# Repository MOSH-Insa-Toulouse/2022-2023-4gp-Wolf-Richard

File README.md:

# 2022-2023-4gp-Wolf-Richard

## General Description

One of our projects as part of our 4th year at INSA Toulouse in physical engineering is to create a measuring system for a paper and graphite based strain sensor. We must be able to measure the resistance of this sensor and send it to an android app.

To that we added some elements. One can choose the best gain setting for their sensor thanks to the digital potentiometer controlled by the nunchuk and helped by the OLED screen. The Nunchuk is here to choose the calibrated value for the digital potentiometer. Then, the resistance of the strain gauge is sent to an Android app thanks to a Bluetooth module.

## Deliverables

- PCB shield for Arduino Uno
- Arduino code
- Android APK
- Test bench and protocole used to test the sensor
- Datasheet

## Software versions

- KiCad 6.0.11-0
- Arduino 2.0.4
- MIT app inventor nb192

## PCB shield for Arduino Uno

The whole circuit can be seen in the picture below. Only the pins that are connected to the circuit are welded to the PCB.

## Test Bench and protocole used to test the sensor

The test bench used is shown in the following picture.

To test the sensor, we put it on the bench and try to make it take the shape of the bench as much as possible. We payed attention not to touch the graphite or the aligator clips for the test to be reliable. We took the measurments once we had a stable contact with the bench and a stable value. To determine the displacement of the sensor we used the formula:

displacement = thickness / 2*R_curvature

## User Manual of the circuit and the app

When the arduino is plugged in the program starts automatically.

First, the user needs to calibrate the circuit based on its sensor. Flatten the sensor as much as you can and try to find the best level of the potentiometer to optimise the sensor’s response. To do so, push up on the nunchuk to increase the potentiometer value or push down to decrease. When satisfied, push the C button.

Second, the user is invited to put the sensor in the most deflected position of the test that they want to do and to press C again. This allows for the deflection percentage to be shown on the OLED screen.

From that moment on, the Bluetooth module sends the value of the resistance that was calculated in the program. Thanks to the app one can retrieve the value and see its evolution.

On the app of which you can see a screenshot below, one must first connect to the right Bluetooth module with the button "Let’s go Bluetooth". Once confirmed that the connection was done properly, the toggle "Tic tac boom", which controls the clock, must be on to receive the values. The values are sent by the Bluetooth module every 500ms. The button "Send to Grisolia" saves a text file with the values of the resistance in it. It is only clickable when the clock is off.

One can also select a point on the graph and see its value in the orange box. Above is displayed the value received at the moment by the app. Once a measurment done, the graph can be cleared thanks to the "Clear" button.

## Problems and improvements

We discovered too late (as the put the sheild on the Arduino) that our pin which was supposed to be connected to the +5V output pin was in fact connected to the Vin pin which delivers 4.3V. To solve that problem we cut the Vin pin and connected a cable from it to the +5V output.

We had problems using the rotary encoder, as a turn could be registered by the program even if no one had touched it. In the end, we just replaced it by the nunchuk which is much more precise and has way more functionnalities.

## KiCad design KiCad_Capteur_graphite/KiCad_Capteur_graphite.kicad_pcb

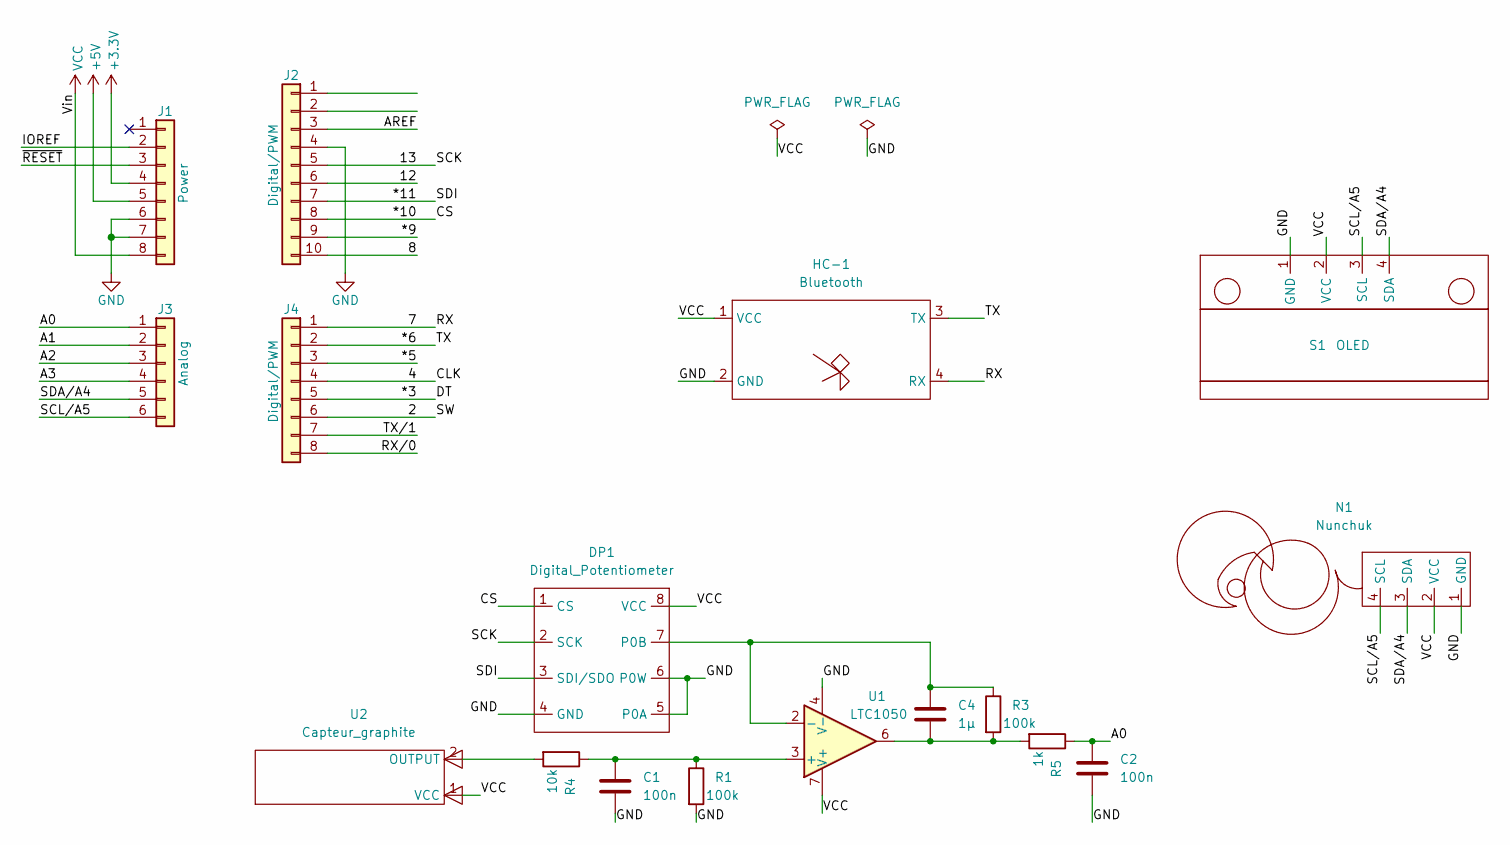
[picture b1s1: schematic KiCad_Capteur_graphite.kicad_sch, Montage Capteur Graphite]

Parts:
C1, C2: 100n; C_moutarde
C4: 1µ; C_rouge
DP1: Digital_Potentiometer; Digital potentimeter
HC-1: Bluetooth; Bluetooth_Empreinte
J1: Power; PinSocket_1x08_P2.54mm_Vertical
J2: Digital/PWM; PinSocket_1x10_P2.54mm_Vertical
J3: Analog; PinSocket_1x06_P2.54mm_Vertical
J4: Digital/PWM; PinSocket_1x08_P2.54mm_Vertical
N1: Nunchuk
R1, R3: 100k; R
R4: 10k; R
R5: 1k; R
S1: OLED
U1: LTC1050
U2: Capteur_graphite

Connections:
+3V3: J1.4
+5V: J1.5
/2: J4.6
/4: J4.4
/7: HC-1.4 (RX), J4.1
/8: J2.10
/12: J2.6
/13: DP1.2 (SCK), J2.5
/*3: J4.5
/*5: J4.3
/*6: HC-1.3 (TX), J4.2
/*9: J2.9
/*10: DP1.1 (CS), J2.8
/*11: DP1.3 (SDI/SDO), J2.7
/A0: C2.2, J3.1, R5.1
/A1: J3.2
/A2: J3.3
/A3: J3.4
/AREF: J2.3
/IOREF: J1.2
/RX/0: J4.8
/SCL/A5: J3.6, N1.4 (SCL), S1.3 (SCL)
/SDA/A4: J3.5, N1.3 (SDA), S1.4 (SDA)
/TX/1: J4.7
/~RESET: J1.3
GND: C1.2, C2.1, DP1.4 (GND), DP1.5 (P0A), DP1.6 (P0W), HC-1.2 (GND), J1.6, J1.7, J2.4, N1.1 (GND), R1.2, S1.1 (GND), U1.4 (V-)
unnamed: C1.1, R1.1, R4.1, U1.3 (+)
unnamed: C4.1, R3.2, R5.2, U1.6
unnamed: C4.2, DP1.7 (P0B), R3.1, U1.2 (-)
unnamed: R4.2, U2.2 (OUTPUT)
VCC: DP1.8 (VCC), HC-1.1 (VCC), J1.8, N1.2 (VCC), S1.2 (VCC), U1.7 (V+), U2.1 (VCC)

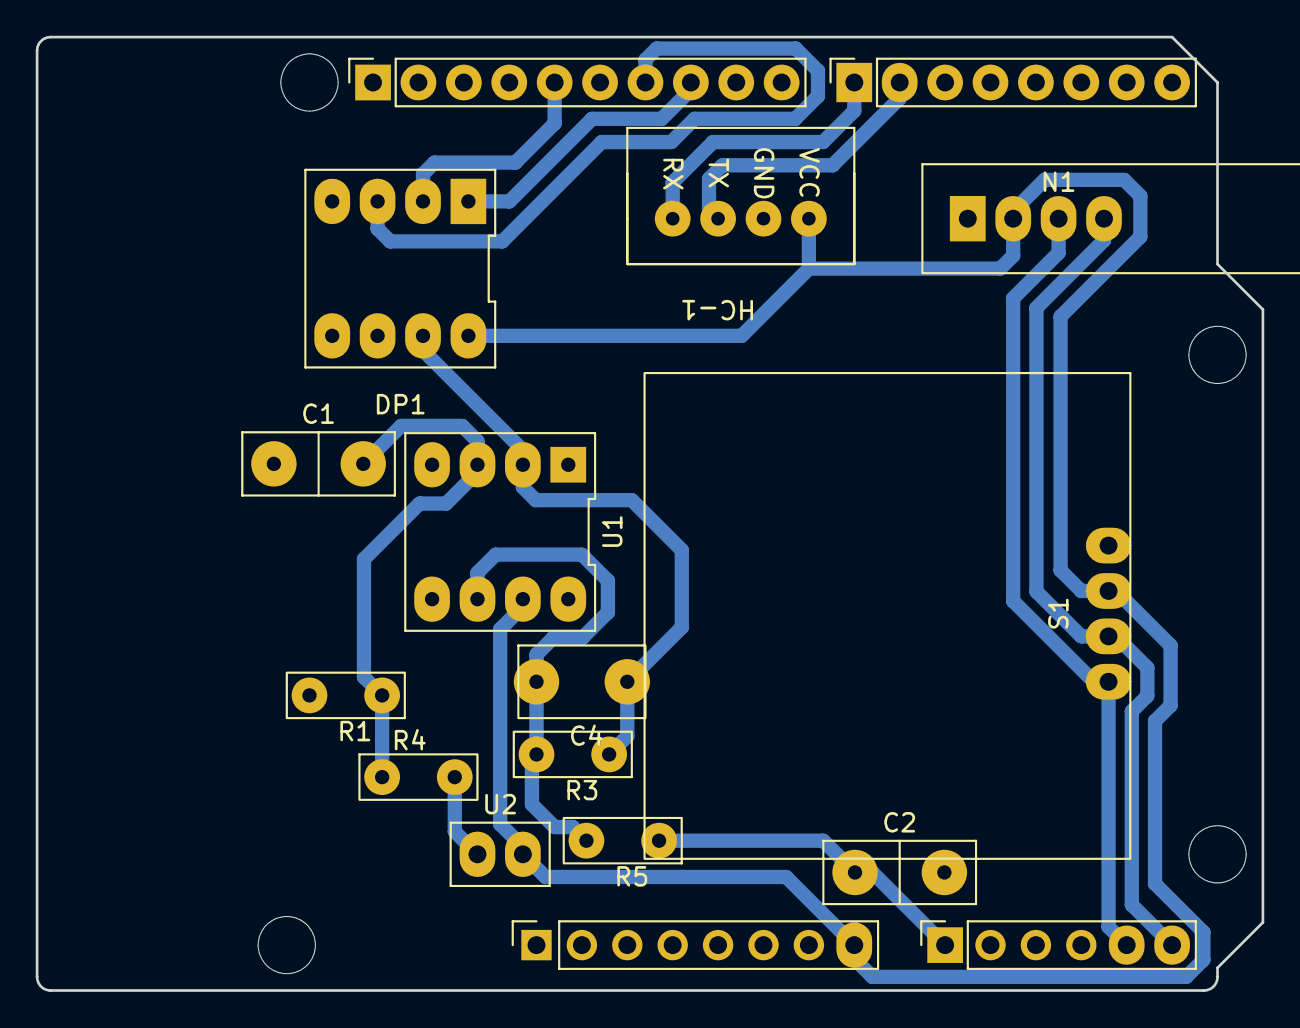
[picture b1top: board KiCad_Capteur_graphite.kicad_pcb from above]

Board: 2 copper layers, 68.6 x 53.3 mm, 21 parts (0 on the bottom side), 14 nets.

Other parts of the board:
MH1, MH2, MH3, MH4: MountingHole_3.2mm

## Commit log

2023-02-03 Changes to be committed: modified: README.md
2023-04-13 adding the main parts
2023-04-16 upload
2023-04-16 add Datasheet
2023-04-16 + readme
2023-04-17 add app
2023-05-26 adding pictures and gitignore DS_Store
